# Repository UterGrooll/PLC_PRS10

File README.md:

# PLC_PRS10

ПЛК ПРС-10 на Arduino + Ethernet. Использую для своих задач в Rapid SCADA: два реле, местный датчик DS18B20 и четыре дискретных входа.

Обмен — `Modbus TCP Slave`, библиотека [ModbusTCP_RU](https://github.com/UterGrooll/ModbusTCP_RU) `0.3.0`, Ethernet `W5100/W5500`.

## Возможности

- Управление двумя реле из SCADA.
- Автоматическое отключение первого реле через 60 секунд.
- Чтение температуры DS18B20 с точностью передачи 0,1 °C.
- Четыре дискретных входа с антидребезгом 50 мс.
- Восстановление Modbus-сервера после возврата Ethernet-линка W5500.

## Аппаратная часть

| Узел | Пин Arduino |
| --- | --- |
| Реле 1 | D7 |
| Реле 2 | D6 |
| DI1 | D2 |
| DI2 | D3 |
| DI3 | D4 |
| DI4 | D5 |
| DS18B20 | D9 |
| W5100/W5500 CS | D10 |

Реле включаются уровнем `HIGH`, при запуске оба выключены (`LOW`). Входы работают через `INPUT_PULLUP`: замкнутый на GND контакт — активный вход.

Ethernet использует стандартные пины SPI платы.

## Сеть

| Параметр | Значение |
| --- | --- |
| IP | `192.168.1.179` |
| MAC | `02:47:A1:10:00:02` |
| Шлюз / DNS | `192.168.1.1` |
| Маска | `255.255.255.0` |
| Порт Modbus TCP | `502` |

Для проверки нужен доступ к сети `192.168.1.0/24`. При необходимости сетевые параметры меняются в начале скетча. MAC и IP не должны совпадать с другим устройством в сети.

## Карта Modbus

Адреса в таблице начинаются с нуля. Coils, Discrete Inputs и Input Registers — отдельные области памяти.

| Область | FC | Address | Назначение |
| --- | --- | --- | --- |
| Coil | 01 / 05 / 15 | 0 | Реле 1, D7; авто-отключение через 60 с |
| Coil | 01 / 05 / 15 | 1 | Реле 2, D6 |
| Discrete Input | 02 | 0 | DI1, D2 |
| Discrete Input | 02 | 1 | DI2, D3 |
| Discrete Input | 02 | 2 | DI3, D4 |
| Discrete Input | 02 | 3 | DI4, D5 |
| Input Register | 04 | 0 | Местная температура DS18B20, °C × 10 |

Для реле: `0 = OFF`, `1 = ON`. Повторная команда ON не продлевает таймер реле 1; для нового цикла нужны OFF → ON. Время задаётся константой `RELAY1_TIMEOUT` в скетче. Настройки времени через Holding Registers здесь нет.

Для входов: `1 = замкнут / LOW`, `0 = разомкнут / HIGH`.

Температура передаётся как **Signed 16-bit**: `253 = 25,3 °C`, `-55 = -5,5 °C`. Значение `32767` означает ошибку или отсутствие измерения; его нельзя пересчитывать в температуру.

## Настройка Modbus Poll

Connection → Connect:

| Параметр | Значение |
| --- | --- |
| Connection | Modbus TCP/IP |
| IP | `192.168.1.179` |
| Server Port | `502` |
| Slave ID | `1` |
| Response Timeout | `1000 ms` |

Read/Write Definition:

| Что читать | Function | Address | Quantity |
| --- | --- | --- | --- |
| Реле | 01 Read Coils | 0 | 2 |
| Входы | 02 Read Discrete Inputs | 0 | 4 |
| Температура | 04 Read Input Registers | 0 | 1 |

Scan Rate для начала — `1000 ms`. При вводе этих адресов отключить `PLC Addresses (Base 1)`.

Запись реле выполняется через `05 Write Single Coil`: Address `0` для первого реле или `1` для второго, Value `ON/OFF`. Команду записи отправлять однократно.

Для температуры выбрать Signed 16-bit и делить значение на 10 в SCADA.

## Восстановление Ethernet

При старте вызываются `Ethernet.begin(mac, ip, dnsServer, gateway, subnet)` и `mb.begin()`.

После пропадания и устойчивого возврата `LinkON` на W5500 выдерживается не менее 1,5 с, затем `mb.restart()` закрывает старые клиентские соединения. Повторного `Ethernet.begin()` и блокирующей паузы в этом обработчике нет. SCADA или Modbus Poll должны подключиться заново.

W5100 может возвращать `Unknown` в `linkStatus()`. Это не вызывает периодического сброса Ethernet.

Это контроль Ethernet-соединения, **не аппаратный watchdog AVR**. Аппаратный watchdog в этом скетче не включён.

## Прошивка

Актуальный скетч: [firmware/plc_prs10/plc_prs10.ino](firmware/plc_prs10/plc_prs10.ino).

Зависимости:

- `SPI` — входит в Arduino core.
- `Ethernet 2.0.2`.
- [ModbusTCP_RU 0.3.0](https://github.com/UterGrooll/ModbusTCP_RU).
- `GyverDS18`.

Размеры памяти Modbus задаются в общем файле библиотеки `src/ModbusTCP_RU_config.h`, а не через локальные `#define` в скетче.

Скетч собран для Arduino UNO и Nano ATmega328P Old Bootloader: `16820` байт Flash, `771` байт SRAM. Проверка сборки не заменяет испытания этой версии на плате.

После заливки проверить реле, четыре входа, температуру, авто-отключение реле 1 и переподключение после возврата кабеля. Реле проверять на безопасной нагрузке.

## Материалы

- [schematic/](schematic/) — исходники схемы.
- [case/](case/) — модель корпуса.
- [screenshot/](screenshot/) — фотографии и изображения.
- [src/](src/) — предыдущие скетчи; для текущей заливки используется только `firmware/plc_prs10/`.

---

by UterGrooll
2026

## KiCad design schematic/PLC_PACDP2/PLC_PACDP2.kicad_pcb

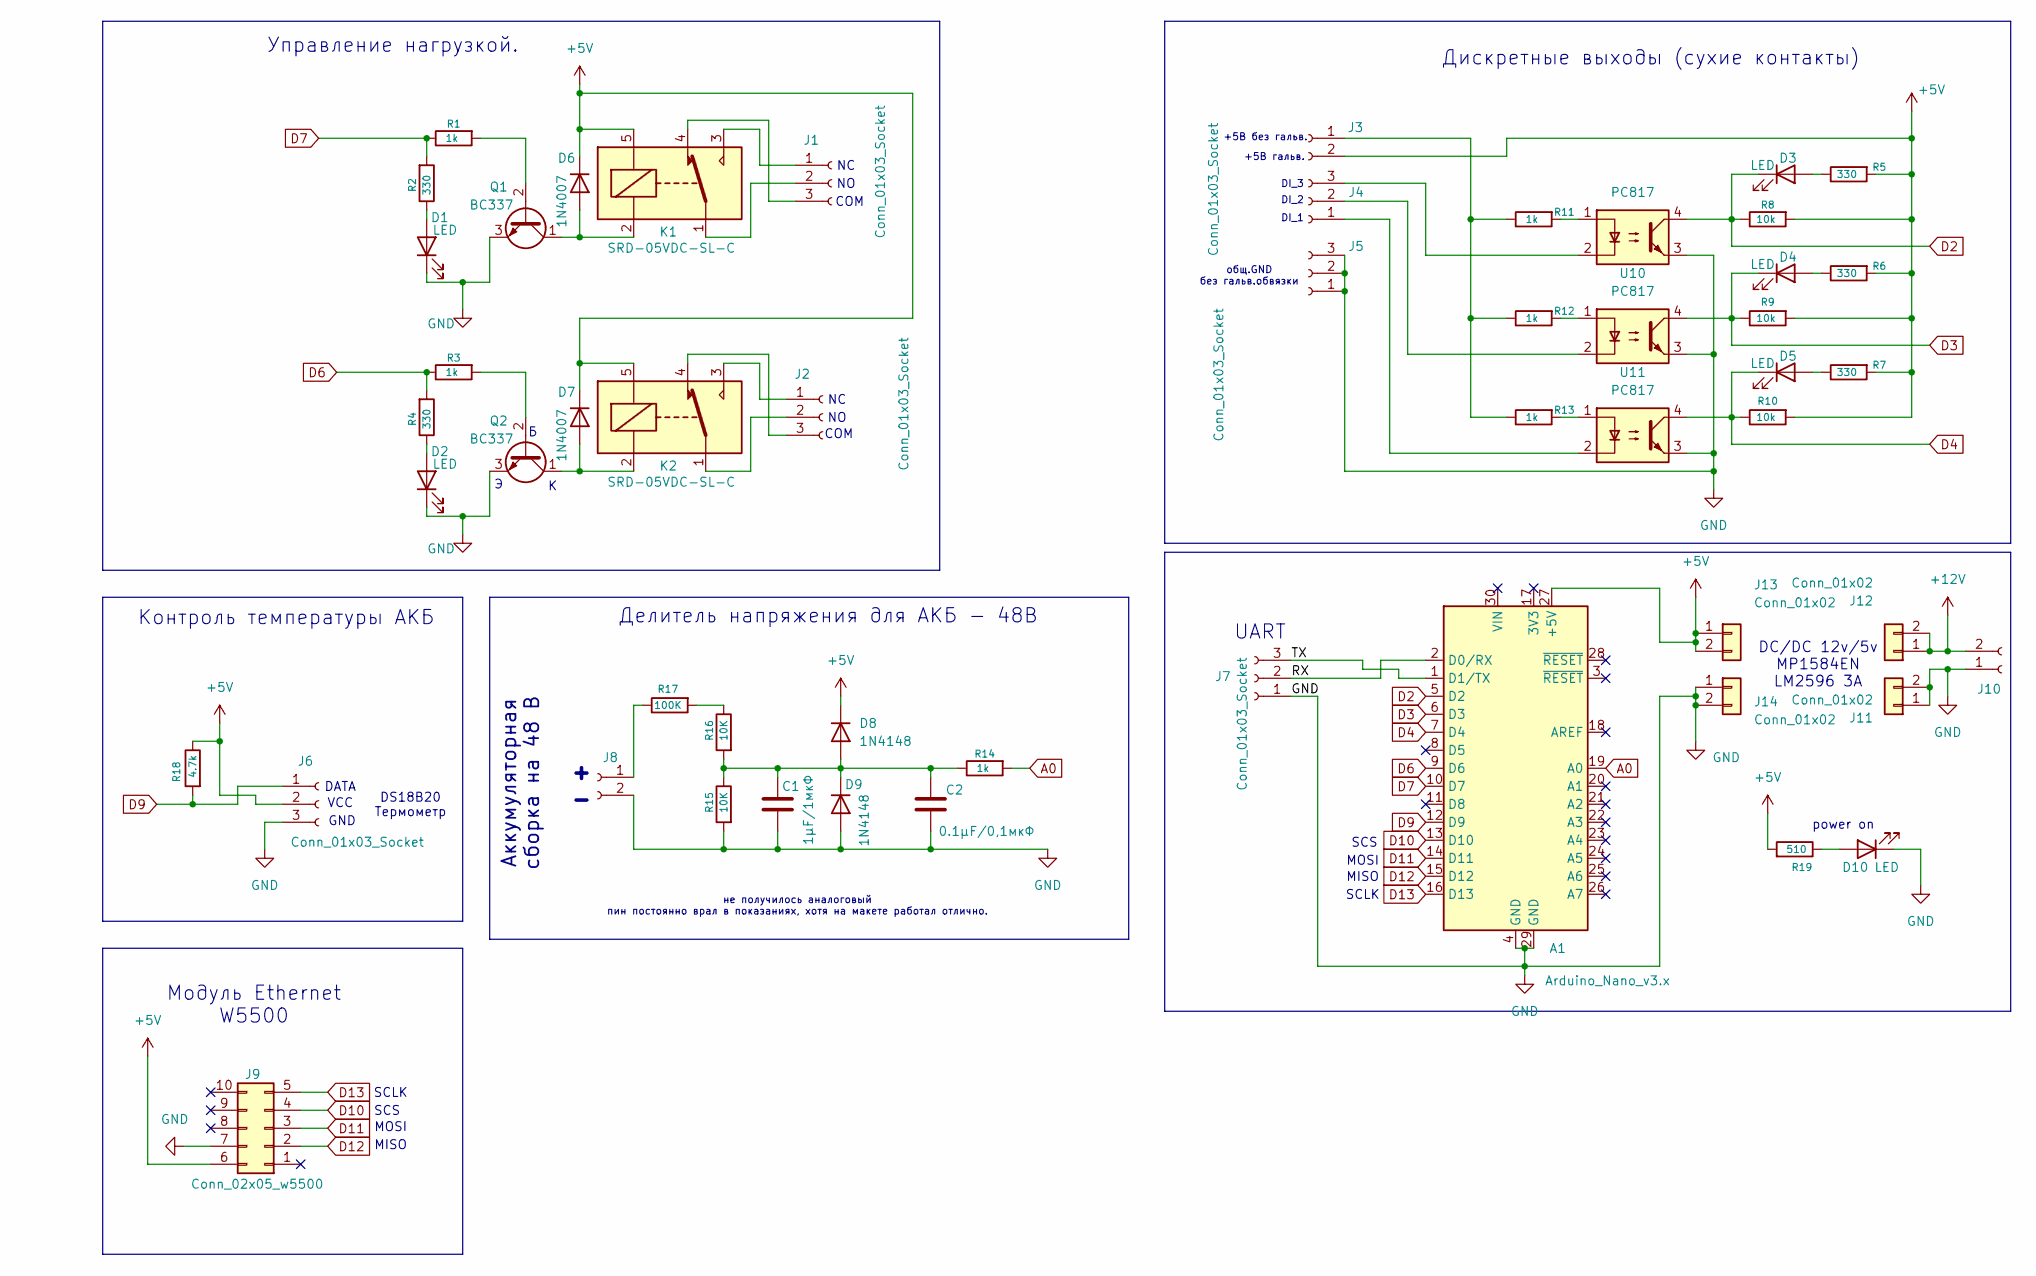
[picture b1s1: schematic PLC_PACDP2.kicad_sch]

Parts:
A1: Arduino_Nano_v3.x; Arduino_Nano
C1: 1µF/1мкФ; C_Rect_L4.6mm_W2.0mm_P2.50mm_MKS02_FKP02
C2: 0.1µF/0,1мкФ; C_Disc_D7.5mm_W2.5mm_P5.00mm
D1, D2, D3, D4, D5, D10: LED; LED_D5.0mm_Clear
D6, D7: 1N4007; D_DO-41_SOD81_P10.16mm_Horizontal
D8, D9: 1N4148; D_DO-35_SOD27_P7.62mm_Horizontal
J1, J2, J4, J5, J6: Conn_01x03_Socket; TerminalBlock_Phoenix_MKDS-1,5-3-5.08_1x03_P5.08mm_Horizont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
J3, J10: Conn_01x02_Socket; TerminalBlock_Phoenix_MKDS-1,5-2-5.08_1x02_P5.08mm_Horizont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; PartNumber KLS2-128-5.00-02P-4S
J7: Conn_01x03_Socket; PinSocket_1x03_P2.54mm_Vertical
J8: Conn_01x02_Socket; TerminalBlock_MetzConnect_Type703_RT10N02HGLU_1x02_P9.52mm_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; PartNumber KLS2-128-5.00-02P-4S
J9: Conn_02x05_w5500; PinSocket_2x05_P2.54mm_Vertical
J11, J12, J13, J14: Conn_01x02; PinSocket_1x02_P2.54mm_Vertical
K1, K2: SRD-05VDC-SL-C; Relay_SPDT_SANYOU_SRD_Series_Form_C
Q1, Q2: BC337; TO-92_Inline
R1, R3, R11, R12, R13, R14: 1k; R_Axial_DIN0207_L6.3mm_D2.5mm_P10.16mm_Horizontal; PartNumber RC0805FR-07510RL
R2, R4, R5, R6, R7: 330; R_Axial_DIN0207_L6.3mm_D2.5mm_P10.16mm_Horizontal; PartNumber RC0805FR-07510RL
R8, R9, R10: 10k; R_Axial_DIN0207_L6.3mm_D2.5mm_P10.16mm_Horizontal; PartNumber RC0805FR-07510RL
R15, R16: 10K; R_Axial_DIN0207_L6.3mm_D2.5mm_P10.16mm_Horizontal; PartNumber RC0805FR-07510RL
R17: 100K; R_Axial_DIN0207_L6.3mm_D2.5mm_P10.16mm_Horizontal; PartNumber RC0805FR-07510RL
R18: 4.7k; R_Axial_DIN0207_L6.3mm_D2.5mm_P10.16mm_Horizontal; PartNumber RC0805FR-07510RL
R19: 510; R_Axial_DIN0207_L6.3mm_D2.5mm_P10.16mm_Horizontal; PartNumber RC0805FR-07510RL
U9, U10, U11: PC817; DIP-4_W7.62mm

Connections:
+5V: A1.27 (+5V), D6.1 (K), D7.1 (K), D8.1 (K), J3.2, J6.2, J9.6 (+5), J13.1, J13.2, K1.5, K2.5, R5.2, R6.2, R7.2, R8.2, R9.2, R10.2, R18.1, R19.2
+12V: J10.2, J12.1, J12.2
/RX: A1.2 (D0/RX), J7.2
/TX: A1.1 (D1/TX), J7.3
D2: A1.5 (D2), D3.1 (K), R8.1, U9.4
D3: A1.6 (D3), D4.1 (K), R9.1, U10.4
D4: A1.7 (D4), D5.1 (K), R10.1, U11.4
D6: A1.9 (D6), R3.1, R4.2
D7: A1.10 (D7), R1.1, R2.2
D9: A1.12 (D9), J6.1, R18.2
D10: A1.13 (D10), J9.4 (SCS)
D11: A1.14 (D11), J9.3 (MOSI)
D12: A1.15 (D12), J9.2 (MISO)
D13: A1.16 (D13), J9.5 (SCLK)
GND: A1.4 (GND), A1.29 (GND), C1.2, C2.2, D1.1 (K), D2.1 (K), D9.2 (A), D10.1 (K), J5.1, J5.2, J5.3, J6.3, J7.1, J8.2, J9.7 (GND), J10.1, J11.1, J11.2, J14.1, J14.2, Q1.3 (E), Q2.3 (E), R15.2, U9.3, U10.3, U11.3
unnamed: D1.2 (A), R2.1
unnamed: D2.2 (A), R4.1
unnamed: D3.2 (A), R5.1
unnamed: D4.2 (A), R6.1
unnamed: D5.2 (A), R7.1
unnamed: D6.2 (A), K1.2, Q1.1 (C)
unnamed: D7.2 (A), K2.2, Q2.1 (C)
unnamed: C1.1, C2.1, D8.2 (A), D9.1 (K), R14.1, R15.1, R16.2
unnamed: D10.2 (A), R19.1
unnamed: J1.1, K1.3
unnamed: J1.2, K1.1
unnamed: J1.3, K1.4
unnamed: J2.1, K2.3
unnamed: J2.2, K2.1
unnamed: J2.3, K2.4
unnamed: J3.1, R11.1, R12.1, R13.1
unnamed: J4.1, U11.2
unnamed: J4.2, U10.2
unnamed: J4.3, U9.2
unnamed: J8.1, R17.1
unnamed: Q1.2 (B), R1.2
unnamed: Q2.2 (B), R3.2
unnamed: R11.2, U9.1
unnamed: R12.2, U10.1
unnamed: R13.2, U11.1
unnamed: R16.1, R17.2
А0: A1.19 (A0), R14.2

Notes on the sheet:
Управление нагрузкой.
SCS
DI_3
DI_2
Аккумуляторная сборка на 48 В
Модуль Ethernet W5500
COM
UART
SCLK
DS18B20 Термометр
DATA
MOSI
VCC
Контроль температуры АКБ
GND
MISO
общ.GND без гальв.обвязки
+5В гальв.
DC/DC 12v/5v MP1584EN LM2596 3A
DI_1
+5В без гальв.
power on
не получилось аналоговый пин постоянно врал в показаниях, хотя на макете работал отлично.
Дискретные выходы (сухие контакты)
Делитель напряжения для АКБ - 48В

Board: 2 copper layers, 53 parts (0 on the bottom side), 42 nets, no tracks yet.

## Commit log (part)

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2025-11-16 v.01
2025-11-16 Create README.md
    описание
2026-05-07 Update ModbusTCP_RU SCADA example
